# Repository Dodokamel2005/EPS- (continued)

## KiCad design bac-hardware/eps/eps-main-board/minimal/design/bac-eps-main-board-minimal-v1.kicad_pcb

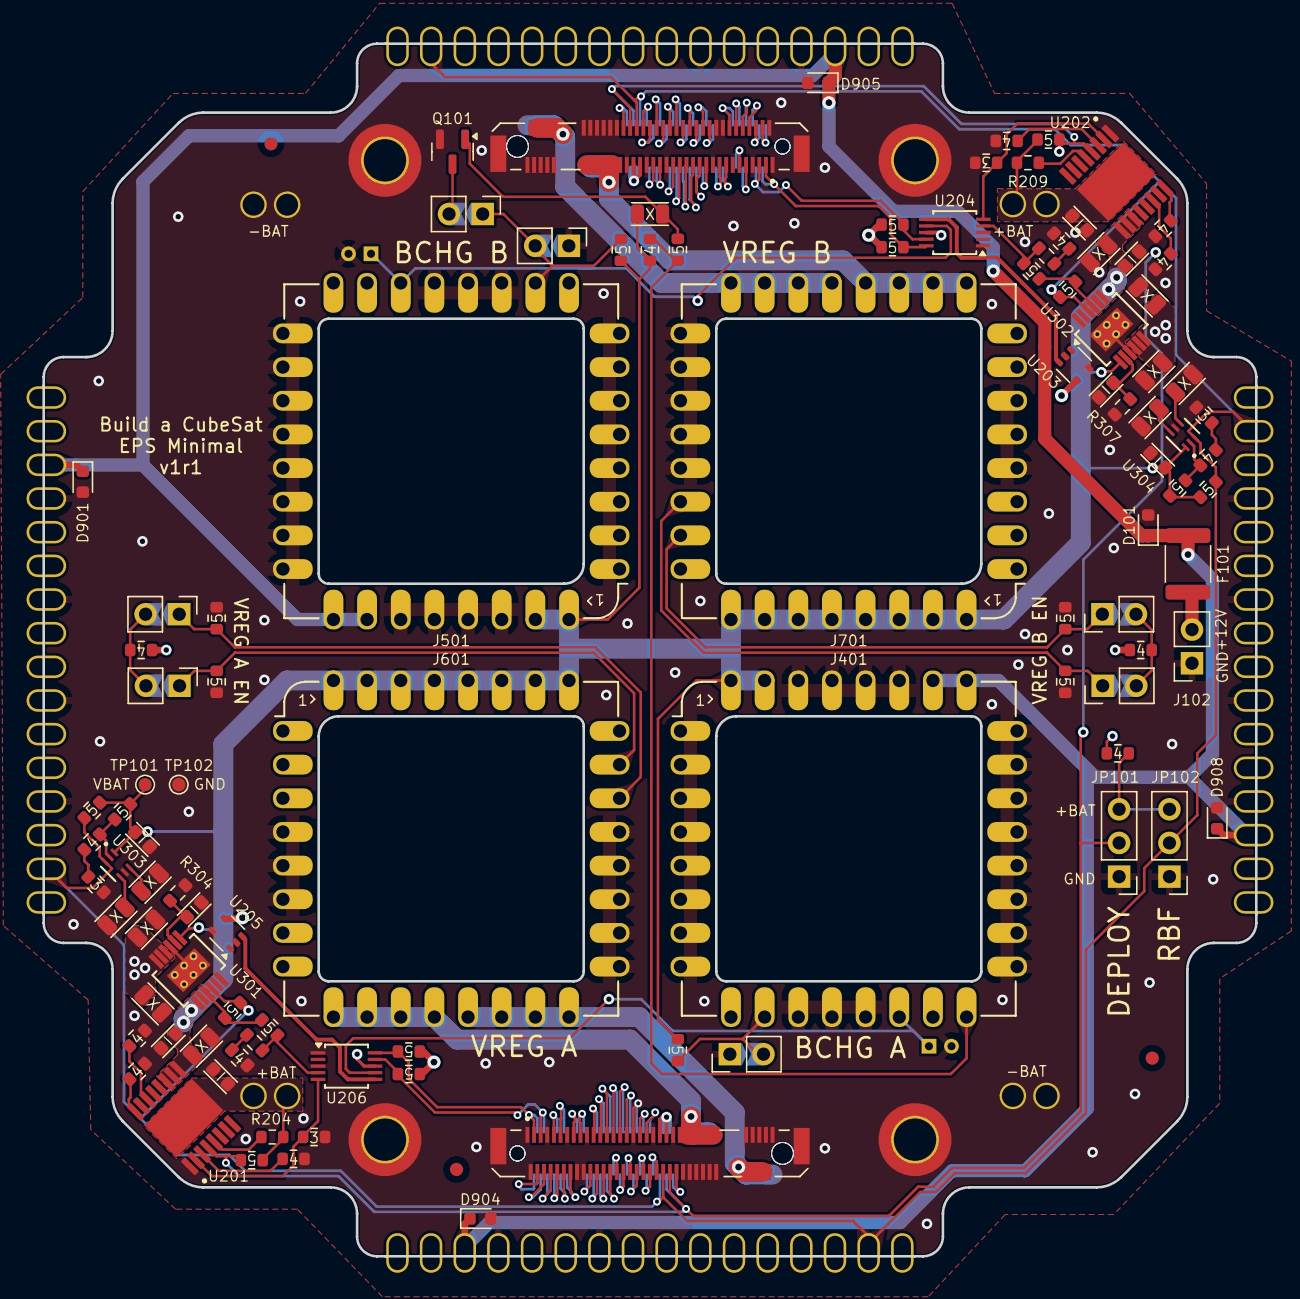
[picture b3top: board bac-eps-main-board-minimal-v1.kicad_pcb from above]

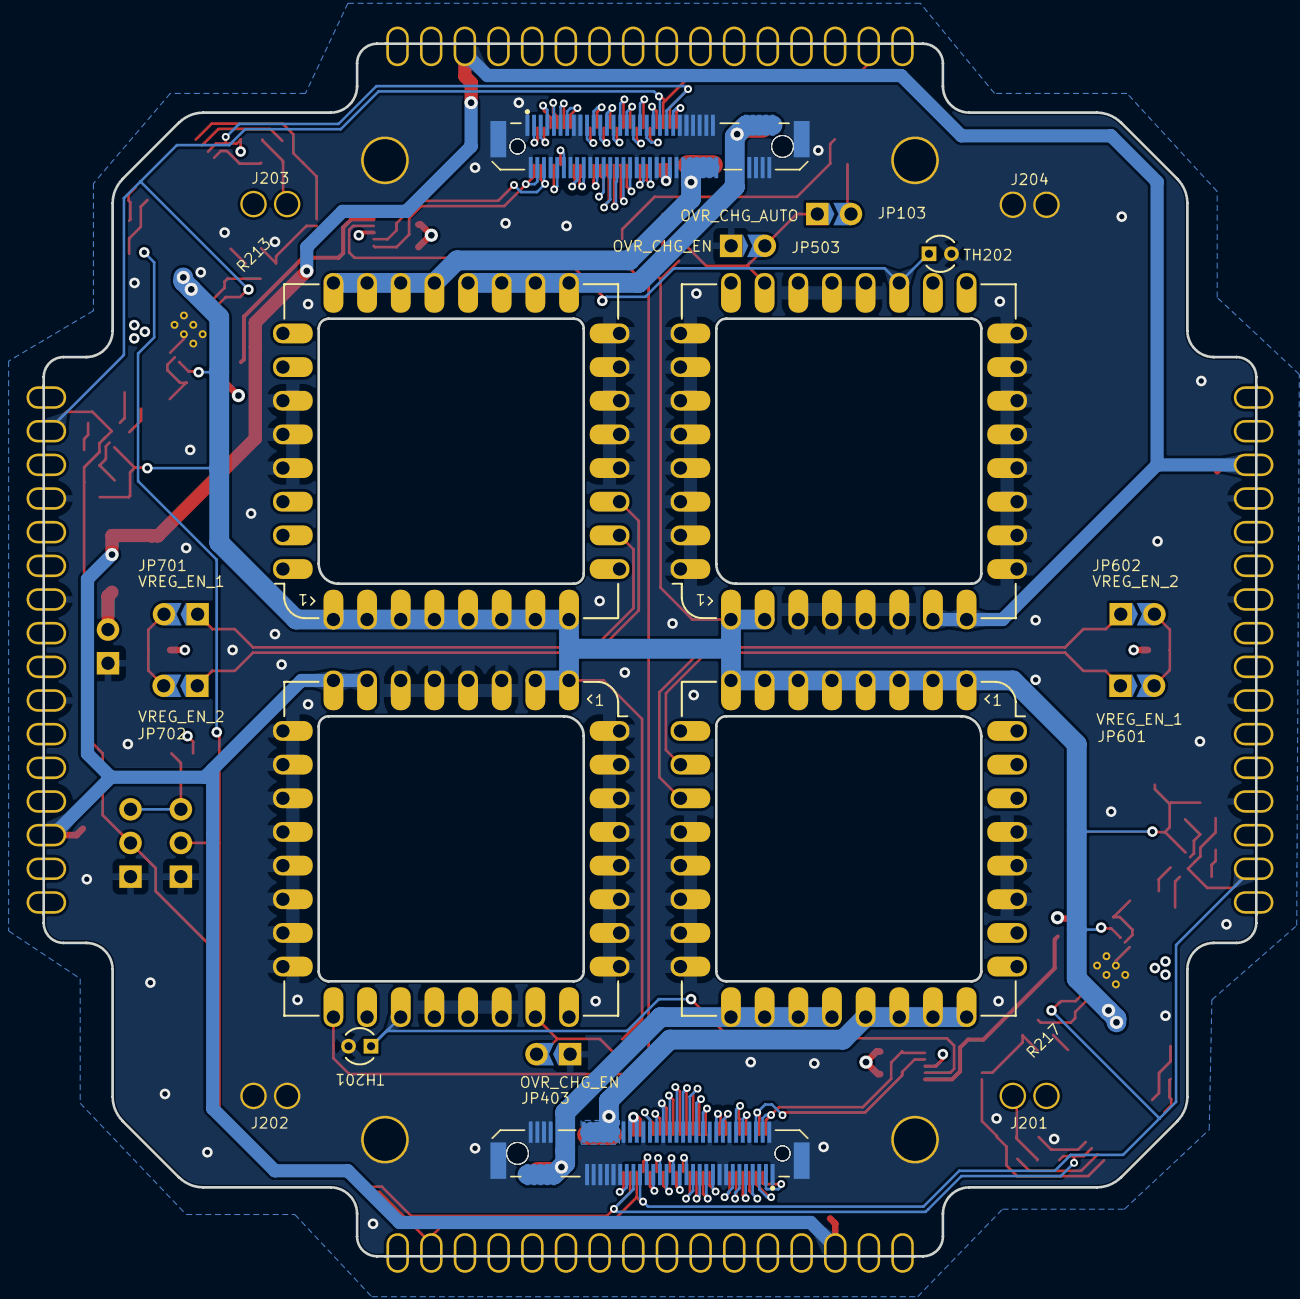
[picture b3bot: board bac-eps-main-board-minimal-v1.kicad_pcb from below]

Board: 4 copper layers, 91.5 x 91.5 mm, 118 parts (8 on the bottom side), 116 nets.

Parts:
C101, C301, C302, C303, C304, C305, C306, C310, C311, C313, C314: 10u; bac-C-0805-10u
C201, C202, C203, C204, C307, C308, C309, C312: 1u; bac-C-0603-1u
D101, D901, D904, D905, D908: TI ESD751; D_0603_1608Metric
F101: 1812L300/24SLER; Fuse_1812_4532Metric
FID101, FID102, FID103: Fiducial; Fiducial_1mm_Mask2mm
H101, H102, H103, H104: M3; MountingHole_3.2mm_M3_ISO14580_Pad_TopOnly
J102: Conn_01x02; PinSocket_1x02_P2.54mm_Vertical
J201, J202, J203, J204: Conn_01x02_Pin; bac-Mill-Max-0630-0-15-15-30-27-10-0-PN-1x02-P2.54
J401, J501, J601, J701: bac-eps-v1-module-landing-pad
J801: AMP MDT350M01001VT; bac-M.2-Key-M-bacBus-Connector-ReflowSolder
J802: AMP MDT350M01001VT; bac-M.2-Key-M-bacBus-Connector-DragSolder
J803: BMP MDT350M01001VT; bac-M.2-Key-M-bacBus-Connector-ReflowSolder
J804: BMP MDT350M01001VT; bac-M.2-Key-M-bacBus-Connector-DragSolder
J901, J902, J903, J904: Panel Connector 1x16; bac-Mill-Max-0630-0-15-15-30-27-10-0-SE-1x16-P2.54
JP101, JP102: Jumper_3_Open; PinHeader_1x03_P2.54mm_Vertical
JP103: OVR_CHG_AUTO; bac-CombinedJumper-2_P2.54mm_Open_THT
JP403, JP503: OVR_CHG_EN; bac-CombinedJumper-2_P2.54mm_Open_THT
JP601, JP701: VREG_EN_1; bac-CombinedJumper-2_P2.54mm_Open_THT
JP602, JP702: VREG_EN_2; bac-CombinedJumper-2_P2.54mm_Open_THT
Q101: DMN62D0U-7; SOT-23
R102, R104, R112, R211, R212, R215, R218, R219, R220, R221, R222, R301, R302, R303, R305, R309, R310, R601, R602, R701, R702: 100k; bac-R-0603-100k
R103, R105, R106, R107, R201, R202, R203, R206, R207, R208, R214, R216, R306, R311: 10k; bac-R-0603-10k
R204, R209, R213, R217: 16k; R_0603_1608Metric
R205, R210: 3.3k; bac-R-0603-1k
R304, R307: 33.2k; R_0603_1608Metric
R308, R312: 1k; bac-R-0603-1k
TH201, TH202: NTC 10k; Cantherm-MF52A1103F3380
TP101, TP102: TestPoint; TestPoint_Pad_D1.0mm
U201, U202: TI TPS1HB08AQPWPRQ1; TI-TPS1HB08AQPWPRQ1
U203, U205: TMP235A2DCKR; SOT-353_SC-70-5
U204, U206: ADS1115IDGS; TSSOP-10_3x3mm_P0.5mm
U301, U302: ADI LT3045HMSE; ADI-LT3045HMSE
U303, U304: TPS3842A650DRLRQ1; TI-TPS3842

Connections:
+3V3: C302.1, C303.1, C305.1, C306.1, J401.24, J501.24, J601.9, J701.9, J801.41, J801.43, J802.42, J802.44, J803.41, J803.43, J804.42, J804.44, J901.8, J901.9, J902.8, J902.9, J903.8, J903.9, J904.8, J904.9, R106.1, R107.1, R219.1, R220.1, R221.1, R222.1, U203.4 (V_{DD}), U204.8 (VDD), U205.4 (V_{DD}), U206.8 (VDD), U301.10 (OUTS), U301.11 (OUT), U301.12 (OUT), U302.10 (OUTS), U302.11 (OUT), U302.12 (OUT)
+12V: F101.2, J102.2
+BAT: C201.2, C202.2, J201.1, J201.2, J203.1, J203.2, R103.1, R204.2, R209.2, R211.1, R212.1, U201.17 (VBB), U202.17 (VBB)
/+3V3_MAIN_A: J601.21, J601.22, J601.23, J601.24, J801.47, J801.49, J801.51, J801.53, J801.55, J801.57, J802.48, J802.50, J802.52, J802.54, J802.56, J802.58
/+3V3_MAIN_B: J701.21, J701.22, J701.23, J701.24, J803.47, J803.49, J803.51, J803.53, J803.55, J803.57, J804.48, J804.50, J804.52, J804.54, J804.56, J804.58
/+5V_MAIN_A: J601.17, J601.18, J601.19, J601.20, J801.68, J801.70, J801.72, J801.74, J802.67, J802.69, J802.71, J802.73, J802.75
/+5V_MAIN_B: J701.17, J701.18, J701.19, J701.20, J803.68, J803.70, J803.72, J803.74, J804.67, J804.69, J804.71, J804.73, J804.75
/BACBUS_A_CAN_1_N: J801.15, J802.16
/BACBUS_A_CAN_1_P: J801.17, J802.18
/BACBUS_A_I2C_1_SCL: J801.3, J802.4, R219.2, U206.10 (SCL)
/BACBUS_A_I2C_1_SDA: J801.5, J802.6, R220.2, U206.9 (SDA)
/BACBUS_B_CAN_1_N: J803.15, J804.16
/BACBUS_B_CAN_1_P: J803.17, J804.18
/BACBUS_B_I2C_1_SCL: J803.3, J804.4, R221.2, U204.10 (SCL)
/BACBUS_B_I2C_1_SDA: J803.5, J804.6, R222.2, U204.9 (SDA)
/BAT_NTC_A: J401.19, TH201.1, U206.7 (AIN3)
/BAT_NTC_B: J501.19, TH202.1, U204.7 (AIN3)
/BCHG_A_FAULT: JP103.2 (B), Q101.3 (D)
/Battery Charger Module A/EN: J401.23, JP403.2 (B), R104.2
/Battery Charger Module A/~FAULT: J401.17, R105.2, R112.1
/Battery Charger Module B/EN: J501.23, JP103.1 (A), JP503.2 (B), R102.2
/Battery Pack/VSNS_1: R205.1, U201.2 (SNS), U206.5 (AIN1)
/Battery Pack/VSNS_2: R210.1, U202.2 (SNS), U204.5 (AIN1)
/DEPLOY_1: J801.44, J802.43, J803.44, J804.43, JP101.2 (C), R211.2, R212.2, U201.4 (EN), U202.4 (EN)
/DEPLOY_2/RBF: J801.42, J802.41, J803.42, J804.41, J901.2, J902.2, J903.2, J904.2, JP102.2 (C), R301.1, R302.1, R303.2, R309.2, U301.4 (EN/UB), U302.4 (EN/UB), U303.3 (~RESET), U304.3 (~RESET)
/LDOs/UV_SNS_1: R305.1, R306.2, U303.2 (SENSE)
/LDOs/UV_SNS_2: R310.1, R311.2, U304.2 (SENSE)
/VBAT: C101.1, C203.2, C204.2, C301.1, C304.1, C307.1, C312.1, J401.1, J401.2, J501.1, J501.2, J601.1, J601.2, J601.3, J601.4, J601.5, J601.6, J601.7, J601.8, J701.1, J701.2, J701.3, J701.4, J701.5, J701.6, J701.7, J701.8, R102.1, R104.1, R105.1, R215.1, R218.1, R301.2, R302.2, R303.1, R305.2, R309.1, R310.2, TP101.1, U201.9 (VOUT), U201.10 (VOUT), U201.11 (VOUT), U202.9 (VOUT), U202.10 (VOUT), U202.11 (VOUT), U301.1 (IN), U301.2 (IN), U301.3 (IN), U301.7 (PGFB), U302.1 (IN), U302.2 (IN), U302.3 (IN), U302.7 (PGFB), U303.1 (VDD), U304.1 (VDD)
/VPV: D101.1 (K), D901.1 (K), D904.1 (K), D905.1 (K), D908.1 (K), F101.1, J401.7, J401.8, J501.7, J501.8, J901.14, J902.14, J903.14, J904.14
/Voltage Regulator Module A/EN_1: JP601.2 (B), JP602.2 (B), R106.2
/Voltage Regulator Module B/EN_1: JP701.2 (B), JP702.2 (B), R107.2
/bacBus Connectors/3A: J801.4, J802.3
/bacBus Connectors/3B: J803.4, J804.3
/bacBus Connectors/5A: J801.6, J802.5
/bacBus Connectors/5B: J803.6, J804.5
/bacBus Connectors/7A: J801.8, J802.7
/bacBus Connectors/7B: J803.8, J804.7
/bacBus Connectors/9A: J801.10, J802.9
/bacBus Connectors/9B: J803.10, J804.9
/bacBus Connectors/10A: J801.9, J802.10
/bacBus Connectors/10B: J803.9, J804.10
/bacBus Connectors/11A: J801.12, J802.11
/bacBus Connectors/11B: J803.12, J804.11
/bacBus Connectors/12A: J801.11, J802.12
/bacBus Connectors/12B: J803.11, J804.12
/bacBus Connectors/13A: J801.14, J802.13
/bacBus Connectors/13B: J803.14, J804.13
/bacBus Connectors/19A: J801.20, J802.19
/bacBus Connectors/19B: J803.20, J804.19
/bacBus Connectors/21A: J801.22, J802.21
/bacBus Connectors/21B: J803.22, J804.21
/bacBus Connectors/22A: J801.21, J802.22
/bacBus Connectors/22B: J803.21, J804.22
/bacBus Connectors/23A: J801.24, J802.23
/bacBus Connectors/23B: J803.24, J804.23
/bacBus Connectors/24A: J801.23, J802.24
/bacBus Connectors/24B: J803.23, J804.24
/bacBus Connectors/25A: J801.26, J802.25
/bacBus Connectors/25B: J803.26, J804.25
/bacBus Connectors/26A: J801.25, J802.26
/bacBus Connectors/26B: J803.25, J804.26
/bacBus Connectors/27A: J801.28, J802.27
/bacBus Connectors/27B: J803.28, J804.27
/bacBus Connectors/28A: J801.27, J802.28
/bacBus Connectors/28B: J803.27, J804.28
/bacBus Connectors/29A: J801.30, J802.29
/bacBus Connectors/29B: J803.30, J804.29
/bacBus Connectors/30A: J801.29, J802.30
/bacBus Connectors/30B: J803.29, J804.30
/bacBus Connectors/31A: J801.32, J802.31
/bacBus Connectors/31B: J803.32, J804.31
/bacBus Connectors/32A: J801.31, J802.32
/bacBus Connectors/32B: J803.31, J804.32
/bacBus Connectors/33A: J801.34, J802.33
/bacBus Connectors/33B: J803.34, J804.33
/bacBus Connectors/35A: J801.36, J802.35
/bacBus Connectors/35B: J803.36, J804.35
/bacBus Connectors/36A: J801.35, J802.36
/bacBus Connectors/36B: J803.35, J804.36
/bacBus Connectors/37A: J801.38, J802.37
/bacBus Connectors/37B: J803.38, J804.37
/bacBus Connectors/38A: J801.37, J802.38
/bacBus Connectors/38B: J803.37, J804.38
/bacBus Connectors/39A: J801.40, J802.39
/bacBus Connectors/39B: J803.40, J804.39
/bacBus Connectors/45A: J801.46, J802.45
/bacBus Connectors/45B: J803.46, J804.45
GND: C201.1, C202.1, C203.1, C204.1, C301.2, C302.2, C303.2, C304.2, C305.2, C306.2, C307.2, C308.1, C309.1, C310.2, C311.2, C312.2, C313.2, C314.2, D101.2 (A), D901.2 (A), D904.2 (A), D905.2 (A), D908.2 (A), H101.1, H102.1, H103.1, H104.1, J102.1, J202.1, J202.2, J204.1, J204.2, J401.3, J401.4, J401.5, J401.6, J401.9, J401.10, J401.11, J401.12, J401.13, J401.14, J401.15, J401.16, J401.20, J401.21, J401.22, J401.25, J401.26, J401.27, J401.28, J401.29, J401.30, J401.31, J401.32, J501.3, J501.4, J501.5, J501.6, J501.9, J501.10, J501.11, J501.12, J501.13, J501.14, J501.15, J501.16, J501.20, J501.21, J501.22, J501.25, J501.26, J501.27, J501.28, J501.29, J501.30, J501.31, J501.32, J601.12, J601.13, J601.14, J601.15, J601.16, J601.27, J601.28, J601.29, J701.12, J701.13, J701.14, J701.15, J701.16, J701.27, J701.28, J701.29, J801.1, J801.2, J801.7, J801.13, J801.16, J801.18, J801.19, J801.33, J801.39, J801.45, J801.48, J801.50, J801.52, J801.54, J801.56, J801.58, J801.67, J801.69, J801.71, J801.73, J801.75, J801.S1 (SHIELD), J801.S2 (SHIELD__1), J802.1, J802.2, J802.8, J802.14, J802.15, J802.17, J802.20, J802.34, J802.40, J802.46, J802.47, J802.49, J802.51, J802.53, J802.55, J802.57, J802.68, J802.70, J802.72, J802.74, J802.S1 (SHIELD), J802.S2 (SHIELD__1), J803.1, J803.2, J803.7, J803.13, J803.16, J803.18, J803.19, J803.33, J803.39, J803.45, J803.48, J803.50, J803.52, J803.54, J803.56, J803.58, J803.67, J803.69, J803.71, J803.73, J803.75, J803.S1 (SHIELD), J803.S2 (SHIELD__1), J804.1, J804.2, J804.8, J804.14, J804.15, J804.17, J804.20, J804.34, J804.40, J804.46, J804.47, J804.49, J804.51, J804.53, J804.55, J804.57, J804.68, J804.70, J804.72, J804.74, J804.S1 (SHIELD), J804.S2 (SHIELD__1), J901.4, J901.7, J901.10, J901.13, J902.4, J902.7, J902.10, J902.13, J903.4, J903.7, J903.10, J903.13, J904.4, J904.7, J904.10, J904.13, JP101.1 (A), JP102.1 (A), JP403.1 (A), JP503.1 (A), Q101.2 (S), R201.2, R202.2, R203.2, R205.2, R206.2, R207.2, R208.2, R210.2, R214.2, R216.2, R304.2, R307.2, R308.1, R312.1, R601.2, R602.2, R701.2, R702.2, TH201.2, TH202.2, TP102.1, U201.1 (GND), U202.1 (GND), U203.2 (GND), U203.5 (GND), U204.1 (ADDR), U204.3 (GND), U205.2 (GND), U205.5 (GND), U206.1 (ADDR), U206.3 (GND), U301.6 (ILIM), U301.9 (GND), U301.EPAD (GND), U302.6 (ILIM), U302.9 (GND), U302.EPAD (GND), U303.5 (GND), U304.5 (GND)
unnamed: JP101.3 (B), JP102.3 (B), R103.2
unnamed: J601.10, JP601.1 (A), R601.1
unnamed: J601.11, JP602.1 (A), R602.1
unnamed: J701.10, JP701.1 (A), R701.1
unnamed: J701.11, JP702.1 (A), R702.1
unnamed: C101.2, Q101.1 (G), R112.2
unnamed: R213.2, R214.1
unnamed: R216.1, R217.2
unnamed: R306.1, R308.2
unnamed: R311.1, R312.2
unnamed: R203.1, U201.16 (DIA_EN)
unnamed: R204.1, U201.5 (ILIM)
unnamed: R201.1, U201.3 (LATCH)
unnamed: R202.1, U201.14 (SEL1)
unnamed: R208.1, U202.16 (DIA_EN)
unnamed: R209.1, U202.5 (ILIM)
unnamed: R206.1, U202.3 (LATCH)
unnamed: R207.1, U202.14 (SEL1)
unnamed: U203.3 (V_{OUT}), U204.6 (AIN2)
unnamed: R213.1, R215.2, U204.4 (AIN0)
unnamed: U205.3 (V_{OUT}), U206.6 (AIN2)
unnamed: R217.1, R218.2, U206.4 (AIN0)
unnamed: C308.2, R304.1, U301.8 (SET)
unnamed: C309.2, R307.1, U302.8 (SET)
unnamed: C311.1, U303.6 (CTR)
unnamed: C310.1, U303.4 (CTS)
unnamed: C314.1, U304.6 (CTR)
unnamed: C313.1, U304.4 (CTS)

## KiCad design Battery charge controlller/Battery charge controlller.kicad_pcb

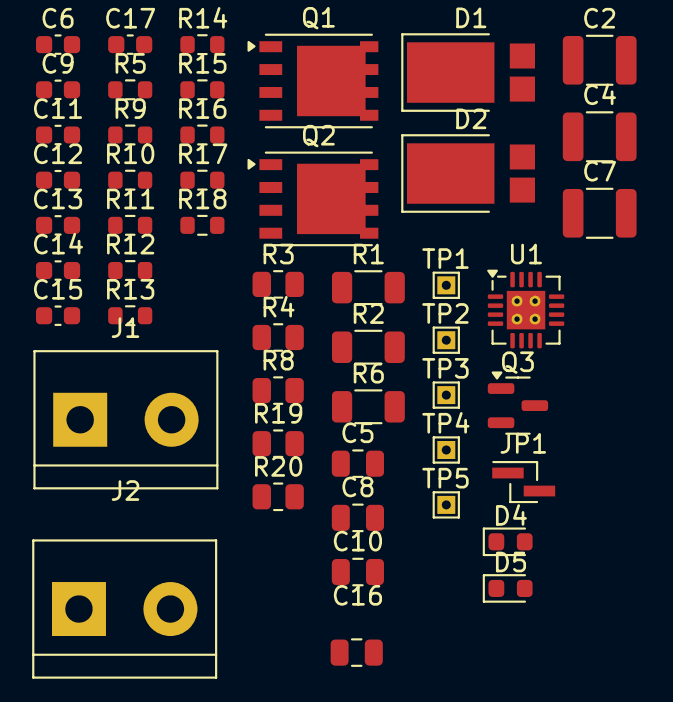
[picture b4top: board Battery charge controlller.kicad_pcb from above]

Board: 2 copper layers, 50 parts (0 on the bottom side), 26 nets, no tracks yet.

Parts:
C2, C7: 10u; C_1210_3225Metric
C4: 2.2u; C_1210_3225Metric
C5, C8, C10, C16: 1u; C_0805_2012Metric
C6, C11, C12, C14: 0.1u; C_0603_1608Metric
C9, C13: 1u; C_0603_1608Metric
C15, C17: 22p; C_0603_1608Metric
D1: PDS1040; D_PowerDI-5
D2: MBR0530; D_PowerDI-5
D4, D5: LED; D_0603_1608Metric
J1: 14V; TerminalBlock_bornier-2_P5.08mm
J2: Conn_01x03; TerminalBlock_bornier-2_P5.08mm
JP1: Conn_01x03; PinHeader_1x02_P1.00mm_Vertical_SMD_Pin1Left
Q1, Q2: Si7336ADP; PowerPAK_SO-8_Single
Q3: 2N7002; SOT-23
R1, R2: 3.9k; R_1206_3216Metric
R3, R4: 10; R_0805_2012Metric
R5: 2.2; R_0603_1608Metric
R6: 0.02; R_1206_3216Metric
R8: 10k; R_0805_2012Metric
R9: 5.23k; R_0603_1608Metric
R10: 0.001; R_0603_1608Metric
R11: 100; R_0603_1608Metric
R12: 30.1k; R_0603_1608Metric
R13: 499k; R_0603_1608Metric
R14: 10k; R_0603_1608Metric
R15: 100k; R_0603_1608Metric
R16: R; R_0603_1608Metric
R17, R18: 10K; R_0603_1608Metric
R19: 499k; R_0805_2012Metric
R20: 36K; R_0805_2012Metric
TP1, TP2, TP4, TP5: TestPoint; TestPoint_THTPad_1.0x1.0mm_Drill0.5mm
TP3: TestPoint_Probe; TestPoint_THTPad_1.0x1.0mm_Drill0.5mm
U1: BQ24650; Texas_RVA_VQFN-16-1EP_3.5x3.5mm_P0.5mm_EP2.14x2.14mm_Therma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

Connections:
GND: C2.2, C4.2, C5.1, C7.2, C8.2, C10.2, C11.2, C12.2, C13.2, C16.2, J1.1, Q2.1 (S), Q2.2 (S), Q2.3 (S), Q3.3 (D), R8.2, R12.2, R14.2, R15.2, R16.2, R20.2, U1.11 (GND)
MPPSET: C17.2, Q3.2 (S), R19.2, R20.1, U1.2 (MPPSET)
unnamed: C4.1, R1.2, R2.2
unnamed: C9.2, R8.1
unnamed: C15.1, R10.2, R13.1, TP4.1
unnamed: C2.1, D1.1 (K), Q1.5 (D), R3.1, R4.1
unnamed: C6.2, D2.1 (K), R5.2
unnamed: D4.2 (A), R18.2
unnamed: D5.2 (A), R17.2
unnamed: JP1.1, R14.1
unnamed: JP1.2, R9.2, R11.1, R12.1
unnamed: Q1.4 (G), TP1.1, U1.15 (HIDRV)
unnamed: C6.1, C9.1, Q1.1 (S), Q1.2 (S), Q1.3 (S), Q2.5 (D), TP3.1, U1.14 (PH)
unnamed: Q2.4 (G), U1.13 (LODRV)
unnamed: R5.1, TP2.1, U1.16 (BTST)
unnamed: C12.1, C14.1, R6.1, U1.10 (SRP)
unnamed: C13.1, R11.2, U1.4 (TS)
unnamed: C5.2, R3.2, R4.2, U1.1 (VCC)
unnamed: C15.2, R13.2, R15.1, U1.8 (VFB)
REGN: C10.1, D2.2 (A), U1.12 (REGN)
STAT1: D4.1 (K), U1.3 (STAT1)
STAT2: D5.1 (K), U1.5 (STAT2)
TERM_EN: R16.1, U1.7 (TERM_EN)
V-BATT: C7.1, C8.1, C11.1, C14.2, R6.2, R10.1, TP5.1, U1.9 (SRN)
VIN: C17.1, D1.2 (A), J1.2, R1.1, R2.1, R17.1, R18.1, R19.1
VREF: C16.1, R9.1, U1.6 (VREF)

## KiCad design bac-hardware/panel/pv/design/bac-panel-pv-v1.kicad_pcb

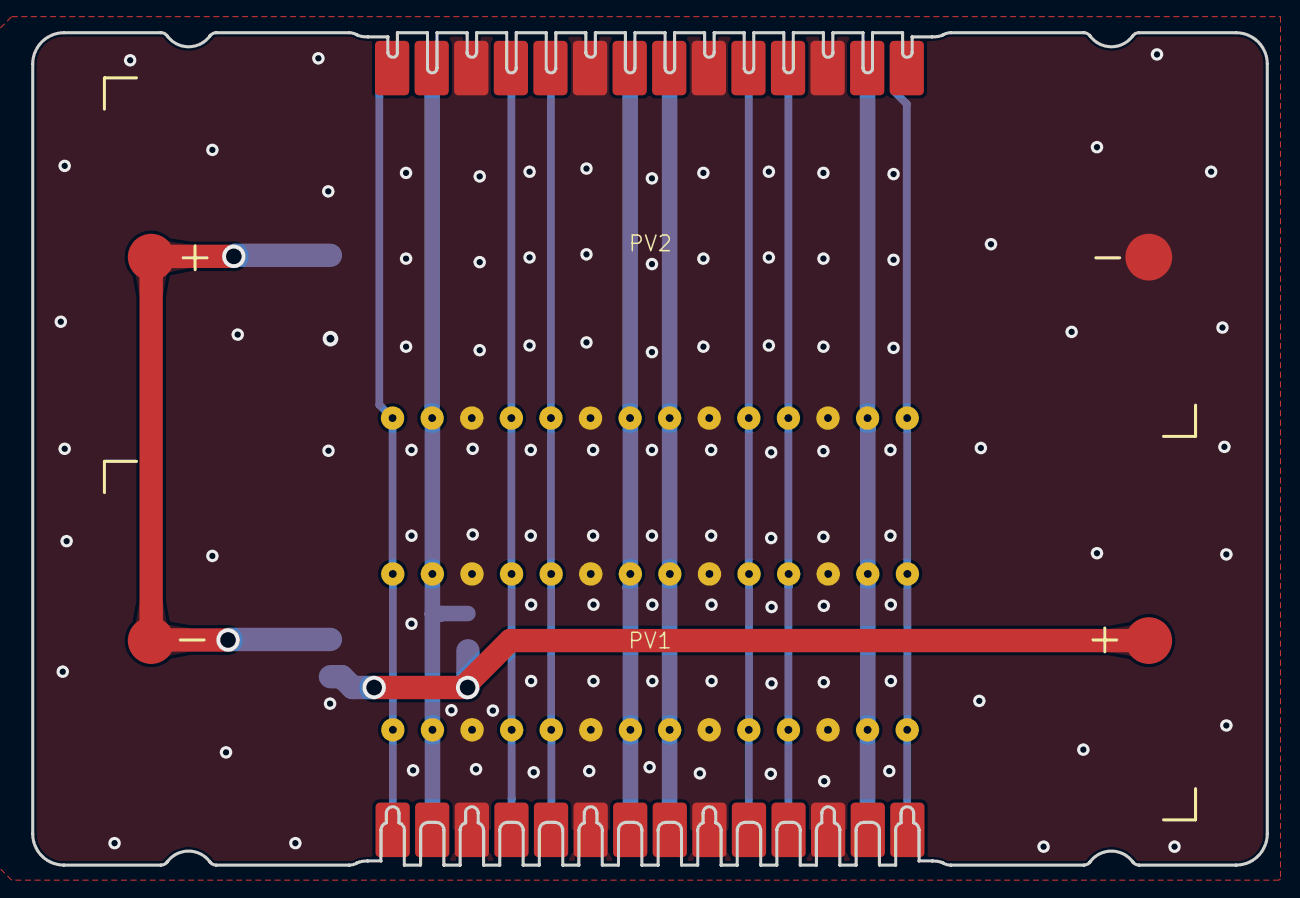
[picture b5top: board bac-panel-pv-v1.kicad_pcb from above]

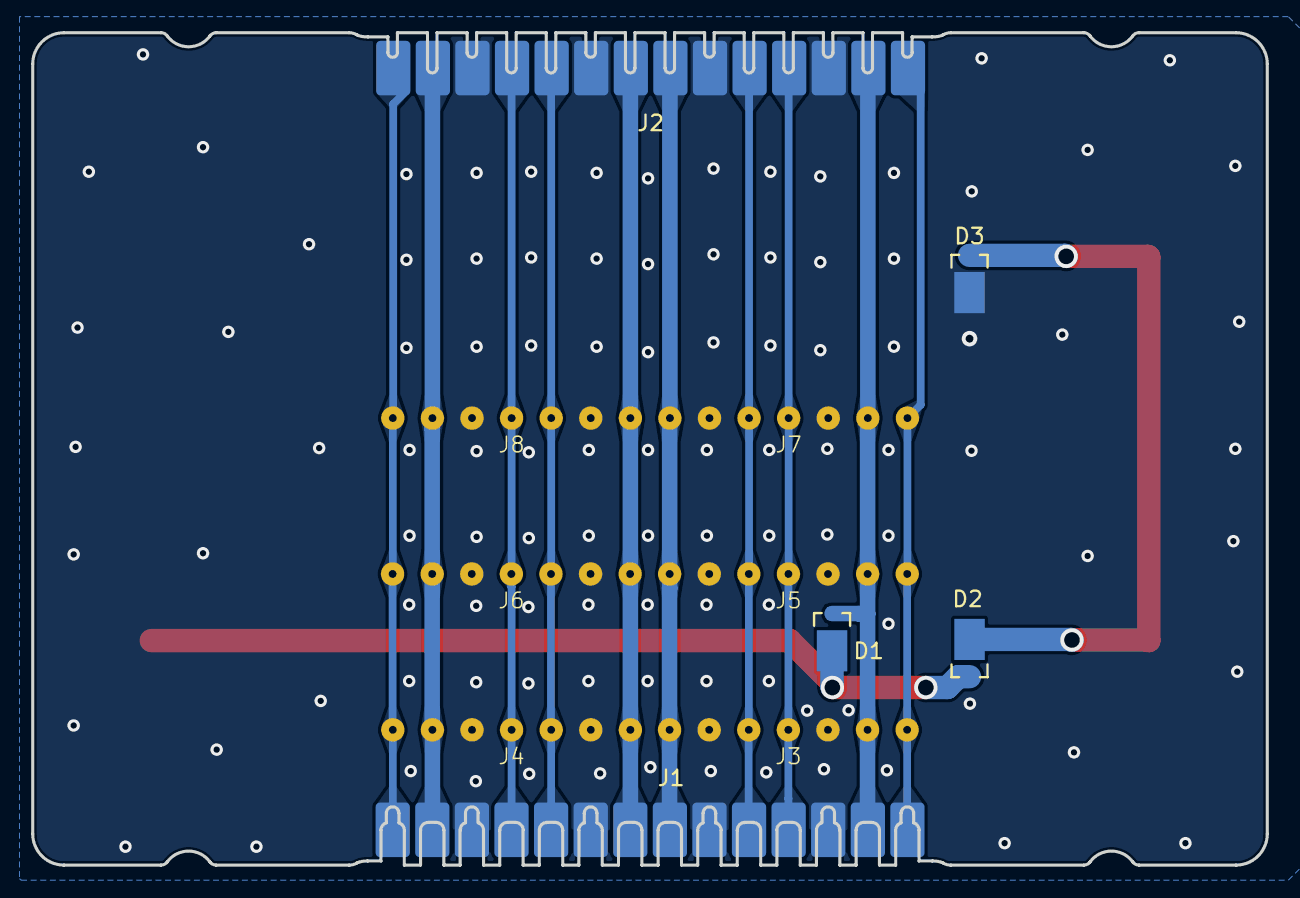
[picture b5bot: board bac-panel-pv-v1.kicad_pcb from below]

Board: 2 copper layers, 79.2 x 53.4 mm, 13 parts (11 on the bottom side), 13 nets.

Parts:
D1, D2, D3: D_Schottky; STM-STPS1L30MF
J1: Panel Connector 1x16; bac-panel-v1-14P-pad-row-receptacles
J2: Panel Connector 1x16; bac-panel-v1-14P-pad-row-pins
J3, J4, J5, J6, J7, J8: Conn_01x07_Socket; Mill-Max-399-10-107-10-009000
PV1, PV2: Solar_Cell; Anysolar-SM141K10TF

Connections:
/3v3_A: J1.7, J2.7, J3.7, J5.7, J7.7
/3v3_B: J1.8, J2.8, J4.1, J6.1, J8.1
/DEPLOY_2/RBF: J1.1, J2.1, J3.1, J5.1, J7.1
/EN_PANEL_B: J1.14, J2.14, J4.7, J6.7, J8.7
/PANEL_SCL_A: J1.4, J2.4, J3.4, J5.4, J7.4
/PANEL_SCL_B: J1.11, J2.11, J4.4, J6.4, J8.4
/PANEL_SDA_A: J1.5, J2.5, J3.5, J5.5, J7.5
/PANEL_SDA_B: J1.10, J2.10, J4.3, J6.3, J8.3
/VPV_A: D1.1 (K), J1.2, J2.2, J3.2, J5.2, J7.2
/VPV_B: J1.13, J2.13, J4.6, J6.6, J8.6
GND: D3.2 (A), J1.3, J1.6, J1.9, J1.12, J2.3, J2.6, J2.9, J2.12, J3.3, J3.6, J4.2, J4.5, J5.3, J5.6, J6.2, J6.5, J7.3, J7.6, J8.2, J8.5, PV2.2 (-)
unnamed: D1.2 (A), D2.1 (K), PV1.1 (+)
unnamed: D2.2 (A), D3.1 (K), PV1.2 (-), PV2.1 (+)

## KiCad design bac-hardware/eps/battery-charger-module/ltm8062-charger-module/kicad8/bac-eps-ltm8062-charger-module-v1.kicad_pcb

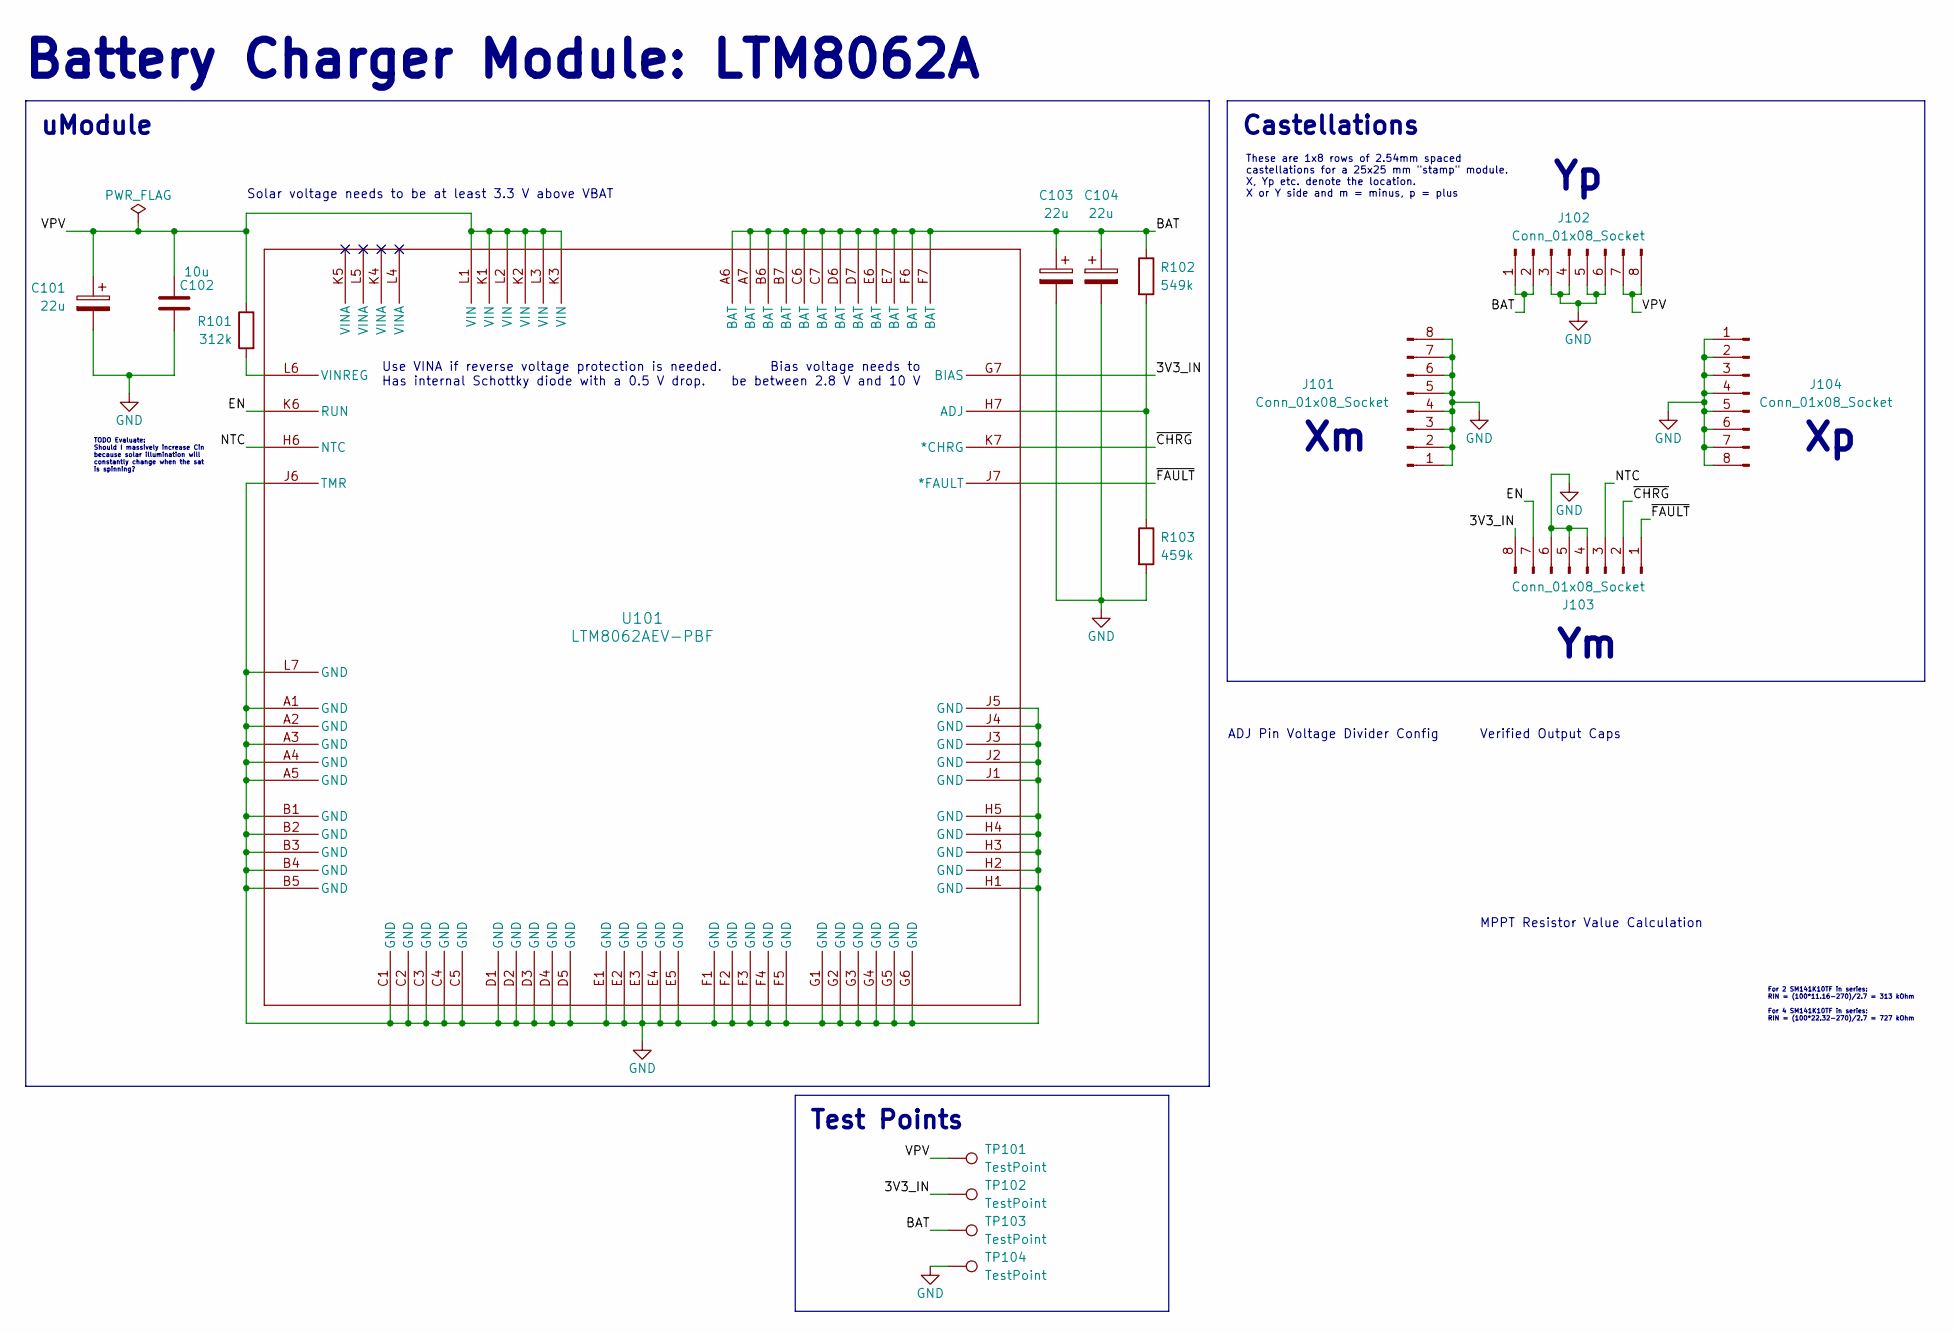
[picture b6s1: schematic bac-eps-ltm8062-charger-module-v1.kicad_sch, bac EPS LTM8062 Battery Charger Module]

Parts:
C101, C103, C104: 22u; CP_EIA-7343-30_AVX-N; Rated Voltage 25V; Tolerance 20%
C102: 10u; C_0603_1608Metric; Tolerance 10%; Voltage Rating 25 V
J101, J102, J103, J104: Conn_01x08_Socket; bac-eps-v1-module-8P-pad-row
R101: 312k; R_0603_1608Metric; Tolerance 0.5%
R102: 549k; R_0603_1608Metric; Tolerance 0.5%
R103: 459k; R_0603_1608Metric; Tolerance 0.5%
TP101, TP102, TP103, TP104: TestPoint; TestPoint_Pad_D1.0mm
U101: LTM8062AEV-PBF; ADI-LTM8062AEV

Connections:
/3V3_IN: J103.8, TP102.1, U101.G7 (BIAS)
/BAT: C103.1, C104.1, J102.1, J102.2, R102.1, TP103.1, U101.A6 (BAT), U101.A7 (BAT), U101.B6 (BAT), U101.B7 (BAT), U101.C6 (BAT), U101.C7 (BAT), U101.D6 (BAT), U101.D7 (BAT), U101.E6 (BAT), U101.E7 (BAT), U101.F6 (BAT), U101.F7 (BAT)
/EN: J103.7, U101.K6 (RUN)
/NTC: J103.3, U101.H6 (NTC)
/VPV: C101.1, C102.1, J102.7, J102.8, R101.1, TP101.1, U101.K1 (VIN), U101.K2 (VIN), U101.K3 (VIN), U101.L1 (VIN), U101.L2 (VIN), U101.L3 (VIN)
/~CHRG: J103.2, U101.K7 (*CHRG)
/~FAULT: J103.1, U101.J7 (*FAULT)
GND: C101.2, C102.2, C103.2, C104.2, J101.1, J101.2, J101.3, J101.4, J101.5, J101.6, J101.7, J101.8, J102.3, J102.4, J102.5, J102.6, J103.4, J103.5, J103.6, J104.1, J104.2, J104.3, J104.4, J104.5, J104.6, J104.7, J104.8, R103.2, TP104.1, U101.A1 (GND), U101.A2 (GND), U101.A3 (GND), U101.A4 (GND), U101.A5 (GND), U101.B1 (GND), U101.B2 (GND), U101.B3 (GND), U101.B4 (GND), U101.B5 (GND), U101.C1 (GND), U101.C2 (GND), U101.C3 (GND), U101.C4 (GND), U101.C5 (GND), U101.D1 (GND), U101.D2 (GND), U101.D3 (GND), U101.D4 (GND), U101.D5 (GND), U101.E1 (GND), U101.E2 (GND), U101.E3 (GND), U101.E4 (GND), U101.E5 (GND), U101.F1 (GND), U101.F2 (GND), U101.F3 (GND), U101.F4 (GND), U101.F5 (GND), U101.G1 (GND), U101.G2 (GND), U101.G3 (GND), U101.G4 (GND), U101.G5 (GND), U101.G6 (GND), U101.H1 (GND), U101.H2 (GND), U101.H3 (GND), U101.H4 (GND), U101.H5 (GND), U101.J1 (GND), U101.J2 (GND), U101.J3 (GND), U101.J4 (GND), U101.J5 (GND), U101.J6 (TMR), U101.L7 (GND)
unnamed: R102.2, R103.1, U101.H7 (ADJ)
unnamed: R101.2, U101.L6 (VINREG)

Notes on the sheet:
Use VINA if reverse voltage protection is needed. Has internal Schottky diode with a 0.5 V drop.
MPPT Resistor Value Calculation
These are 1x8 rows of 2.54mm spaced castellations for a 25x25 mm "stamp" module. X, Yp etc. denote the location. X or Y side and m = minus, p = plus
Bias voltage needs to be between 2.8 V and 10 V
Solar voltage needs to be at least 3.3 V above VBAT
For 2 SM141K10TF in series: RIN = (100*11.16-270)/2.7 = 313 kOhm For 4 SM141K10TF in series: RIN = (100*22.32-270)/2.7 = 727 kOhm
TODO Evaluate: Should I massively increase Cin because solar illumination will constantly change when the sat is spinning?
Verified Output Caps
ADJ Pin Voltage Divider Config
Battery Charger Module: LTM8062A
Test Points
uModule
Castellations

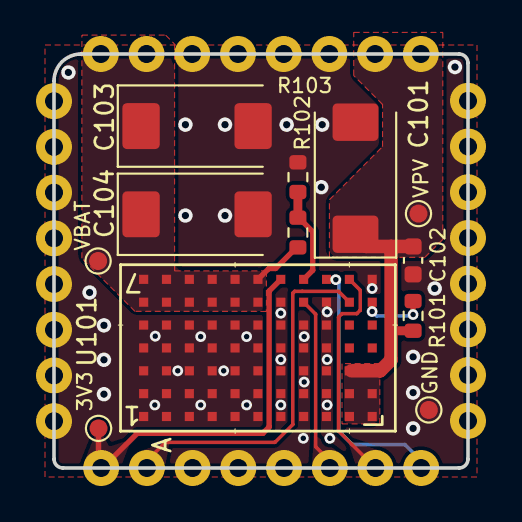
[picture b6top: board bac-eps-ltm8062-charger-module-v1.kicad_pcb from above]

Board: 2 copper layers, 23.0 x 23.0 mm, 16 parts (0 on the bottom side), 10 nets.

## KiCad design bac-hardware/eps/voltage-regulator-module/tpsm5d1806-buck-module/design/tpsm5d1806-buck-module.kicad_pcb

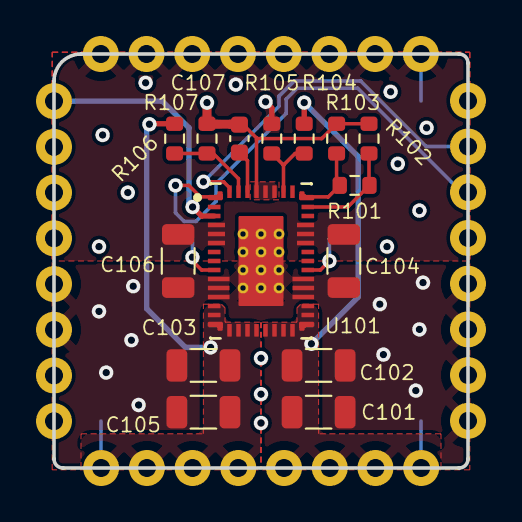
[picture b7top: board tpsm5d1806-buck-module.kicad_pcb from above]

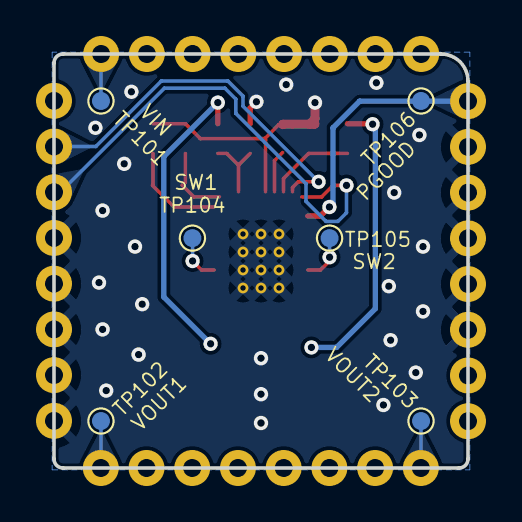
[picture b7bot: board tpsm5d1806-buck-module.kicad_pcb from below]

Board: 4 copper layers, 23.0 x 23.0 mm, 26 parts (6 on the bottom side), 15 nets.

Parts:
C101, C102, C103, C104, C105, C106: 100u; C_1206_3216Metric
C107: 10u; C_0603_1608Metric
J101, J102, J103, J104: Conn_01x08_Socket; bac-eps-v1-module-8P-pad-row
NT101: NetTie_2; NetTie-2_SMD_Pad0.5mm
R101, R105, R107: 10k; R_0603_1608Metric
R102: 15k4; R_0603_1608Metric
R103: 17k4; R_0603_1608Metric
R104: 56k; R_0603_1608Metric
R106: 90k; R_0603_1608Metric
TP101, TP102, TP103, TP104, TP105, TP106: TestPoint; TestPoint_Pad_D1.0mm
U101: TI TPSM5D1806RDBR; TI-TPSM5D1806RDBR

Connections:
/EN1: J104.2, U101.46 (EN2_ISHARE)
/EN2: J104.3, U101.1 (EN1)
/FB1: R104.1, R105.1, U101.40 (FB1)
/FB2: R106.1, R107.1, U101.45 (FB2_VSHARE)
/MODE1: R101.1, R102.1, U101.37 (MODE1)
/MODE2: R101.2, R103.1, U101.38 (MODE2)
/PGOOD1: J101.8, TP106.1, U101.3 (PGOOD1)
/SW1: TP104.1, U101.30 (SW1)
/SW2: TP105.1, U101.9 (SW2)
/VIN: C104.1, C106.1, J102.1, J102.2, J102.3, J102.4, J102.5, J102.6, J102.7, J102.8, TP101.1, U101.4 (VIN), U101.5 (VIN), U101.6 (VIN), U101.33 (VIN), U101.34 (VIN), U101.35 (VIN)
/VOUT1: C101.1, C102.1, J103.1, J103.2, J103.3, J103.4, R104.2, TP102.1, U101.20 (VOUT1), U101.21 (VOUT1), U101.22 (VOUT1), U101.23 (VOUT1), U101.24 (VOUT1), U101.25 (VOUT1), U101.26 (VOUT1)
/VOUT2: C103.1, C105.1, J103.5, J103.6, J103.7, J103.8, R106.2, TP103.1, U101.13 (VOUT2), U101.14 (VOUT2), U101.15 (VOUT2), U101.16 (VOUT2), U101.17 (VOUT2), U101.18 (VOUT2), U101.19 (VOUT2)
GND: C101.2, C102.2, C103.2, C104.2, C105.2, C106.2, J101.3, J101.4, J101.5, J101.6, J101.7, J104.4, J104.5, J104.6, J104.7, J104.8, NT101.2, R105.2, R107.2, U101.10 (PGND), U101.11 (PGND), U101.12 (PGND), U101.27 (PGND), U101.28 (PGND), U101.29 (PGND), U101.47 (PGND), U101.52 (PGND), U101.53 (PGND), U101.54 (PGND), U101.55 (PGND), U101.56 (PGND), U101.57 (PGND), U101.58 (PGND), U101.59 (PGND), U101.60 (PGND), U101.61 (PGND), U101.62 (PGND), U101.63 (PGND)
GNDA: C107.2, NT101.1, R102.2, R103.2, U101.41 (RS-), U101.42 (AGND), U101.43 (AGND)
unnamed: C107.1, U101.44 (BP5)
